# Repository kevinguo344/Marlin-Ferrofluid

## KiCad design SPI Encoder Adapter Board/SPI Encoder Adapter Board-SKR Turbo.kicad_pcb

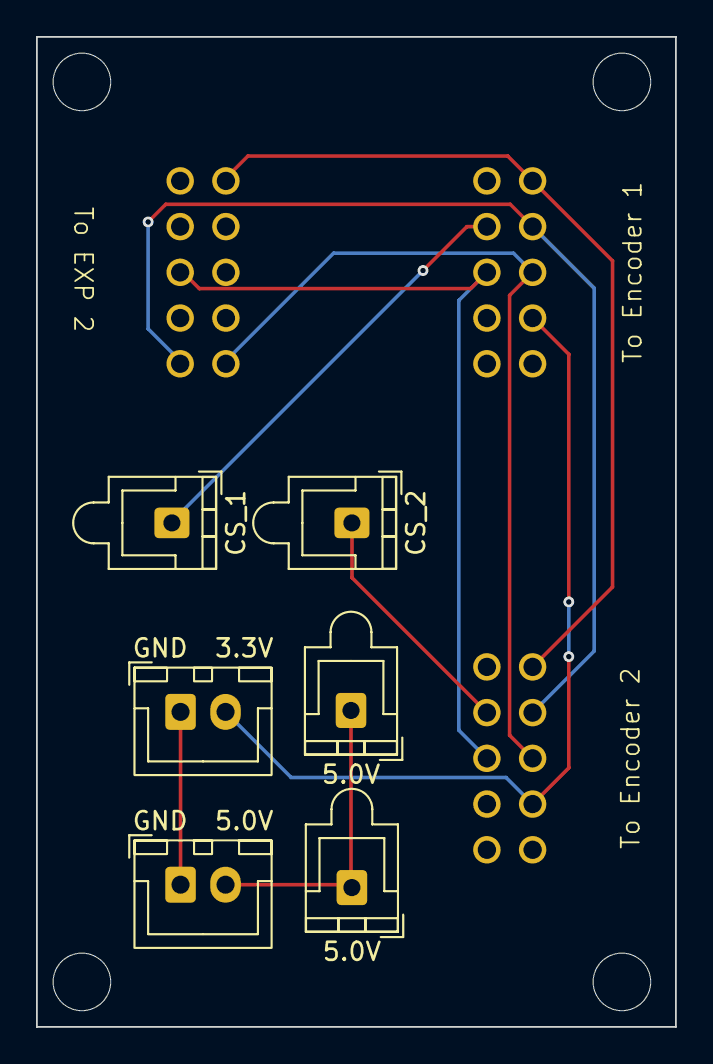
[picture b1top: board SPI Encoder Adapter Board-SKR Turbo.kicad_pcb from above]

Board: 2 copper layers, 35.5 x 55.0 mm, 6 parts (0 on the bottom side), 2 nets.

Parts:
5.0V, 5.0V#2: JST_XH_B1B-XH-AM_1x01_P2.50mm_Vertical
CS_1, CS_2: JST_XH_B1B-XH-AM_1x01_P2.50mm_Vertical
GND  3.3V, GND  5.0V: JST_XH_B2B-XH-A_1x02_P2.50mm_Vertical

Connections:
5.0V: 5.0V.1, 5.0V#2.1, GND 5.0V.2
GND: GND 3.3V.1, GND 5.0V.1

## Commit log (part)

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2026-01-28 configured for Octopus Pro V1.1
2026-01-28 made configuration files align with previous Duet movement and axis configurations
2026-01-28 removed thermal protection since there isn't anything thermal in this machine
2026-01-29 enabled motor driver debugging
2026-01-30 included encoder files - first pass
2026-02-02 changed configuration.h so that it works correctly with corexy config
2026-02-03 changed baudrate to match Max patch settings
2026-02-04 removed AS5047P library (will re-add as customized version later)
2026-02-04 added AS5047P library (original at https://github.com/jonas-merkle/AS5047P)
2026-02-04 added constructor to AS5047P_ComBackend that sets custom custom SPI bus
2026-02-04 implemented custom SPI constructors
2026-02-04 moved SPI encoder code to feature folder, enabled feature so that it will compile correctly
2026-02-05 attempting to clear compiler errors
2026-02-05 increased max speed, acceleration, and jerk
2026-02-06 got includes working, now need to work on getting pin assignments to read correctly
2026-02-06 flattened structure of spi_encoder folder so that util and settings header files actually get used
2026-02-06 added a manager to wrap up encoder operations, added print statments
2026-02-09 angle reading inaccurate, added debug messages
2026-02-10 using much simplified encoder code. Source: ChatGPT (I feel gross)
2026-02-10 added angle readings
2026-02-11 added object wrapper for encoder
2026-02-11 added manager class for SPI Encoders, also added statement that removes null measurements from smoothed values
2026-02-12 changed encoder_update to raw readings
2026-02-12 (DID NOT WORK) attempted to re-add library code to get more descriptive errors
2026-02-12 reverted to using previous library (removing AI generated code) to use dynamic angle error compensation (DAEC). SPI is the same connection as TMC Stepper Drivers.
2026-02-12 started setting up for multi-encoder operation
2026-02-12 moved SPI_Encoder files to modules folder to access homing functions
2026-02-12 added implementation for second encoder
2026-02-13 (DOES NOT WORK) naive implementation of forward kinematics
2026-02-16 live encoder tracking of XY position
2026-02-16 removed redundant defines
2026-02-19 added KiCAD project
2026-02-19 added optimizations to forward kinematics that make it much more memory efficient + speedy
2026-02-19 fixed velocity equation using Q16.16 position numbers, accounted for actual time elapsed from previous encoder reading for velocity, enabled s-curve acceleration
2026-02-20 added idle mode, EMA velocity filter for encoder readings
2026-02-20 added footprint from SparkFun TC78H670FTG as reference
2026-02-23 made EMA optional, cleaned up code, increased rate of updates
2026-02-24 added STEP files for custom PCB
2026-02-25 stopped idle updates, improved placements of PCB traces
2026-02-25 renamed kicad project
2026-02-26 removed port outlines on PCBs
2026-02-26 removed idling param in reportPosition
2026-03-05 moved position of encoders on board, started a velocity LUT for faster calculations
2026-03-20 implemented LUT in on-board velocity calculations
2026-04-06 remove serial printouts for idle updates
2026-05-07 increased motor currents to 1.0A
2026-05-08 changed pins and config for BTT SKR V1.4 Turbo
2026-05-20 changed axis limits to match actual size, disabled encoders temporarily
2026-06-05 added new custom pcb
2026-06-23 updated bed size
2026-06-24 DEBUG MODE, UNDO ONCE COMPLETE
2026-06-26 turned off encoders temporarily
2026-06-30 disabled encoders temporarily
